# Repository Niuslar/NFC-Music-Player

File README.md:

# NFC Album Player

> **Disclaimer:** the software in this repository was written with an AI coding assistant (Claude Code). The project's idea, hardware choices and design decisions are mine, but I did not hand-write the code, so review it before relying on it.

A tabletop music player where each album is a card. Put a card in the slot and its album plays; take it out and it pauses. It runs on a Raspberry Pi Zero 2 W with a proper DAC, a small screen, a knob and four keys, and keeps a whole music collection on its own SD card. Everything you need to build one is here: the software, the wiring, a 3D-printed case and the circuit board behind its keys.

*Render of the case design, made from the same model as its printable parts. The case has not been printed yet.*

## Where to start

The **[project site](https://niuslar.github.io/NFC-Music-Player/)** has the full guides:

| Guide | What is in it |
|---|---|
| [User manual](https://niuslar.github.io/NFC-Music-Player/docs/manual/) | Using the player: [controls](https://niuslar.github.io/NFC-Music-Player/docs/manual/#controls), [linking your first card](https://niuslar.github.io/NFC-Music-Player/docs/manual/#first-card), [settings](https://niuslar.github.io/NFC-Music-Player/docs/manual/#settings), [adding music](https://niuslar.github.io/NFC-Music-Player/docs/manual/#music), the [web remote](https://niuslar.github.io/NFC-Music-Player/docs/manual/#remote) and [lists](https://niuslar.github.io/NFC-Music-Player/docs/manual/#lists) |
| [Electronics guide](https://niuslar.github.io/NFC-Music-Player/docs/) | Building it: [parts](https://niuslar.github.io/NFC-Music-Player/docs/#parts), [preparing the Pi](https://niuslar.github.io/NFC-Music-Player/docs/#flash), [wiring](https://niuslar.github.io/NFC-Music-Player/docs/#wiring), [the front board](https://niuslar.github.io/NFC-Music-Player/docs/#board), [backups and updates](https://niuslar.github.io/NFC-Music-Player/docs/#backup) and [troubleshooting](https://niuslar.github.io/NFC-Music-Player/docs/#trouble) |
| [3D printing guide](https://niuslar.github.io/NFC-Music-Player/NFC-Player-Case/NFC-Player-Printing.html) | Printing the case parts |
| [Assembly guide](https://niuslar.github.io/NFC-Music-Player/NFC-Player-Case/NFC-Player-Assembly.html) | Putting the electronics into the case |

The software is on the [Releases page](https://github.com/Niuslar/NFC-Music-Player/releases). To try the player before buying anything, run the [simulator](#try-it-without-any-hardware).

## What it does

- **Cards are albums.** Blank NFC cards are linked to albums on the player itself, and each card remembers where it stopped. A card can also play a whole artist, or a list of songs from different albums.
- **Hi-Fi sound.** A Raspberry Pi DAC Pro gives 3.5 mm and RCA outputs.
- **Screen and controls.** A 2-inch screen shows the cover, track and time. The knob sets the volume and scrolls lists; four keys do previous, play/pause, next and back.
- **Standby and power.** A press of the power key puts the player on standby, and a card or any key wakes it at once. Holding it for 2 seconds turns the player off safely.
- **Music over USB.** Plug the player into a computer and its music appears as a drive called `MUSIC`.
- **Web remote.** From any phone or computer on the same Wi-Fi: browse the library, play from any track, link cards, upload or delete music and make lists.
- **Settings on the device.** Join a new Wi-Fi network from a phone, set a volume limit, delete music, or restart.
- **Signed updates over Wi-Fi.** **Firmware update** in the settings installs the newest release. The player checks its signature first, and goes back to the previous version if the new one does not start.

## Status

The electronics and software are done and tested on a real Pi. The case is designed but not yet printed.

- Tested on the Pi: the DAC, NFC reader, knob, keys, power key and light, USB drive mode, setup and the web remote, with the 0.91-inch OLED as the screen. The 2-inch ST7789 screen and joining a new Wi-Fi network from the settings have so far been tried only in the simulator.
- The case's printable parts, drawings and source files are in [NFC-Player-Case](NFC-Player-Case).

## Hardware

| Part | Used here |
|---|---|
| Computer | Raspberry Pi Zero 2 W |
| DAC | Raspberry Pi DAC Pro |
| Display | 2-inch ST7789 SPI LCD, 320×240 (a 0.91-inch SSD1306 I2C OLED also works) |
| NFC reader | PN532 over SPI, with NTAG215 cards |
| Knob | 24-click rotary encoder with push switch |
| Keys | Five momentary push buttons: four for playback, one for power |
| Power light | An LED on GPIO 22 |

The full parts list and wiring are in the [electronics guide](https://niuslar.github.io/NFC-Music-Player/docs/).

## Installing the software

### 1. Download a release

From the [Releases page](https://github.com/Niuslar/NFC-Music-Player/releases), download the three files of the newest release into one folder:

- `nfc-player-X.Y.Z.tar.gz`: the player itself
- `manifest.json`: its version, size and SHA-256 checksum
- `manifest.json.sig`: the signature of the manifest

Only the manifest is signed. Its checksum covers the tarball, so a good signature and a matching checksum together mean the tarball is the one that was released.

### 2. Check it

Do this at least before the first install. A player trusts the release key that comes with the first release you install on it, and from then on installs only updates signed by that key, so checking that first release by hand is what makes every later update safe. Updates from the settings, or with `deploy.sh`, are checked for you.

You need `ssh-keygen` from OpenSSH 8.1 or newer. It comes with macOS, Linux and Windows 10 and 11. If it says `unknown option -- Y`, update OpenSSH.

**The release key.** Save this line as a file called `allowed_signers` in the folder with the three files. It is the same as [`system/allowed_signers`](system/allowed_signers) in this repository.

```text
nfc-player-release namespaces="nfc-player-release" ecdsa-sha2-nistp256 AAAAE2VjZHNhLXNoYTItbmlzdHAyNTYAAAAIbmlzdHAyNTYAAABBBNG2z/+2mxTZ/x4zmyfVjZgFa+9KMFRH0Z7DfmxEzkWDxFyXM+AXKKXkTZ2dmMEVd2C32r4rEvr9HIM9+Vl88ME= nfc-player release
```

Its fingerprint is `SHA256:7mMUd2P1uHX7o64klaQmtPYpVBFrPNvpwkcIh9UWavA`.

**Check the signature.** From that folder, on macOS or Linux, or in the Windows Command Prompt:

```sh
ssh-keygen -Y verify -f allowed_signers -I nfc-player-release -n nfc-player-release -s manifest.json.sig < manifest.json
```

In Windows PowerShell, which has no `<`, run it through the Command Prompt:

```powershell
cmd /c "ssh-keygen -Y verify -f allowed_signers -I nfc-player-release -n nfc-player-release -s manifest.json.sig < manifest.json"
```

A good release prints `Good "nfc-player-release" signature for nfc-player-release with ECDSA key SHA256:7mMUd2P1uHX7o64klaQmtPYpVBFrPNvpwkcIh9UWavA`. Anything else means: do not install it, and download it again.

**Check the checksum.** Print the tarball's SHA-256 and compare it with `"sha256"` in `manifest.json`:

| System | Command |
|---|---|
| macOS | `shasum -a 256 nfc-player-X.Y.Z.tar.gz` |
| Linux | `sha256sum nfc-player-X.Y.Z.tar.gz` |
| Windows | `certutil -hashfile nfc-player-X.Y.Z.tar.gz SHA256` |

They must be the same.

### 3. Install it on a new Pi

1. Prepare the Pi as in the electronics guide: [flash the SD card](https://niuslar.github.io/NFC-Music-Player/docs/#flash) with Raspberry Pi OS Lite (64-bit), hostname `nfcplayer` and SSH turned on, [boot it](https://niuslar.github.io/NFC-Music-Player/docs/#boot) and [fit the DAC](https://niuslar.github.io/NFC-Music-Player/docs/#dac).
2. From the folder with the release, copy it to the Pi and run setup. Replace `X.Y.Z` with the version, and use `yourname@nfcplayer.local` if your user name on the Pi is not the same as on your computer. The commands are the same on Windows, macOS and Linux.

   ```sh
   scp nfc-player-X.Y.Z.tar.gz nfcplayer.local:/tmp/
   ```

   ```sh
   ssh -t nfcplayer.local 'mkdir ~/nfc-player-X.Y.Z && tar -xzf /tmp/nfc-player-X.Y.Z.tar.gz -C ~/nfc-player-X.Y.Z && cd ~/nfc-player-X.Y.Z && sudo system/setup.sh'
   ```

   Setup installs the packages it needs, turns on SPI, I2C and USB drive mode, creates the music drive, and installs the player into `/opt/nfc-player`. It also installs the release key, which is why the release must be checked first.
3. Reboot when setup asks to:

   ```sh
   ssh nfcplayer.local 'sudo reboot'
   ```

4. Carry on with [wiring and testing](https://niuslar.github.io/NFC-Music-Player/docs/#wiring) in the electronics guide. The web remote's **Setup** page, at `http://nfcplayer.local/setup`, chooses the screen and knob and tests each part.

The `~/nfc-player-X.Y.Z` folder on the Pi is not needed after setup and can be deleted.

### Updating

**Firmware update** in the player's settings installs the newest release over Wi-Fi. That is the usual way.

To install a release from your computer instead, for a player with no internet connection or to choose the version yourself, download the three files and copy them over:

```sh
scp nfc-player-X.Y.Z.tar.gz manifest.json manifest.json.sig nfcplayer.local:/tmp/
```

```sh
ssh -t nfcplayer.local 'sudo install -d -o nfc-player /var/lib/nfc-player/update && sudo install -o nfc-player -m 644 /tmp/nfc-player-*.tar.gz /tmp/manifest.json /tmp/manifest.json.sig /var/lib/nfc-player/update/ && sudo /usr/local/sbin/nfc-player-update install'
```

This goes through the same steps as **Firmware update**: the player checks the signature, keeps the version it is running, and goes back to it if the new one does not start. It installs only a version newer than the one running. Card links, lists, settings and music are kept.

### With `deploy.sh`

If you have a copy of this repository on macOS or Linux, `deploy.sh` does the checks and the install in one step, on a new Pi or one that is already set up. It checks the signature and checksum against `system/allowed_signers` before sending anything:

```sh
./deploy.sh --release path/to/folder-with-the-three-files
```

```sh
./deploy.sh --release path/to/folder-with-the-three-files yourname@nfcplayer.local
```

Without `--release`, `deploy.sh` copies the working copy of the code to the Pi, for development.

## Try it without any hardware

The simulator shows the screen in a browser and stands in for the knob, keys, cards, USB port and Wi-Fi. You need Python 3.11 or newer.

```sh
python3 -m venv .venv
.venv/bin/pip install pillow numpy python-mpd2 pytest qrcode
.venv/bin/python -m player.demo_library demo/music
.venv/bin/python -m player.main --sim
```

On Windows, use `py` in place of `python3` and `.venv\Scripts\` in place of `.venv/bin/`.

Open `http://localhost:8137` for the simulated player and `http://localhost:8080` for the web remote. The demo library is generated tones, and the simulator is silent unless you run it with MPD (`system/mpd-dev.sh`, then add `--playback mpd`). Add `--display ssd1306` for the small OLED layout, and `--music path/to/your/music` for your own albums (install `mutagen` too, to read their tags).

Run the tests with:

```sh
.venv/bin/python -m pytest
```

## How it is put together

- `player/app.py` is the player's behaviour: a state machine fed with events from cards, controls, USB and the web.
- `player/ui/render.py` draws the screens.
- `player/hw/` holds the drivers (screens, NFC reader, knob and keys, USB drive mode), the simulator, and checks for each part.
- `player/web/` is the web remote, the Setup page, and the page a phone uses to give the player a new Wi-Fi network.
- `player/playback.py` talks to [MPD](https://www.musicpd.org/), which decodes and plays the music.
- `player/wifi.py` reads the Wi-Fi signal and runs the setup network for joining a new one.
- `player/update.py` and `system/nfc-player-update` do updates. The player keeps two copies of itself, in `/opt/nfc-player/a` and `b`. An update goes into the one that is not running, and the player goes back to the other if the new version does not start.
- `system/` has the Pi's setup script, services, root helpers and the release key.
- `NFC-Player-Case/` is the 3D-printed case and the front board, all generated from the dimensions in `case.py`. Its [README](NFC-Player-Case/README.md) explains how to rebuild them.
- `docs/` and the root `index.html` are the project site, served by GitHub Pages from the root of this repository (so the empty `.nojekyll` file has to stay).

## Contributing

Fixes and ideas are welcome. [CONTRIBUTING.md](CONTRIBUTING.md) covers the simulator, the tests and changing the case. For a bug or an idea, open an [issue](https://github.com/Niuslar/NFC-Music-Player/issues).

## Security

- **Updates** are installed only if they are signed by a key in `/etc/nfc-player/allowed_signers` on the player, which setup copies from the first release installed. See [Check it](#2-check-it).
- **The web remote has no password.** Anyone on the same network as the player can control it and add or delete music, and that includes an open network such as a café's. Use it on a home network you trust, or turn it off with `--web-port 0` in `system/nfc-player.service`.
- **Joining a new Wi-Fi network** is guarded separately: the page that takes the password works only on the player's own setup network, whose password is made up fresh each time and shown only on the player's screen.
- **The player runs as its own system user**, which can run only the player's own helpers with `sudo`, so a bug in it cannot take over the Pi.

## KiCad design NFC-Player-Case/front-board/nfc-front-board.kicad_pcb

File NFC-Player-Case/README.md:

# NFC Player Case

The 3D-printed case for the NFC Album Player, and the small board behind its keys: a perfboard you wire yourself, or a printed circuit board. To print and build it, read the [3D printing guide](https://niuslar.github.io/NFC-Music-Player/NFC-Player-Case/NFC-Player-Printing.html) and the [assembly guide](https://niuslar.github.io/NFC-Music-Player/NFC-Player-Case/NFC-Player-Assembly.html). This page is for changing the design.

Every dimension is in [`case.py`](case.py). The other scripts read it, and everything else in this folder is generated from them, so a change always starts in `case.py`. Do not edit the outputs by hand: the next rebuild overwrites them.

## What is here

**Source**

| File | What it does |
|---|---|
| [`case.py`](case.py) | Every dimension and shape, in millimetres. The values marked MEASURE depend on the parts you bought. |
| [`build.py`](build.py) | Builds the STLs and the OpenSCAD copy with Blender, and checks that no two parts collide. |
| [`keycaps.py`](keycaps.py) | The key carrier: four key caps on one printed frame. `build.py` builds it too. |
| [`wood.py`](wood.py) | Optional: carves wood grain from your own `wood-grain.png` into the sides of the chassis. |
| [`drawings.py`](drawings.py) | Draws the dimensioned SVGs. Plain Python, no Blender. |
| [`pictures.py`](pictures.py) | Draws the assembly pictures for the guides. |
| [`render.py`](render.py) | Renders the hero picture, using the scene in `NFC-Player-Render.blend`. |
| [`guide.py`](guide.py) | Writes the printing and assembly guides, and the front board's section of the [electronics guide](../docs/index.html). |
| [`NFC-Player-Render.blend`](NFC-Player-Render.blend) | The render scene: camera, lights, materials and stand-ins for the bought parts. |
| [`front-board/board.py`](front-board/board.py) | Draws, routes and checks the front board in KiCad, and writes the files to order it. |
| [`front-board/perfboard.py`](front-board/perfboard.py) | Lays out the same board on a 70 x 50 mm perfboard, checks its wiring against `board.py`'s schematic and the spacer's openings, and draws it. Plain Python. |

**Generated, and kept in the repository**

| File | Made by |
|---|---|
| [`STL/`](STL) | `build.py` and `keycaps.py`. These are the parts to print. |
| [`NFC-Player-Case.scad`](NFC-Player-Case.scad) | `build.py`. A copy for OpenSCAD users, not yet tried in OpenSCAD. |
| `Front-Panel.svg`, `Rear-Panel.svg`, `Board-Stack.svg`, `Controls-Section.svg`, `Key-Closeup.svg` | `drawings.py` |
| [`NFC-Player-Render.png`](NFC-Player-Render.png) | `render.py` |
| [`NFC-Player-Printing.html`](NFC-Player-Printing.html), [`NFC-Player-Assembly.html`](NFC-Player-Assembly.html) | `guide.py`. These pages are part of the project site. |
| `front-board/nfc-front-board.*` and [`front-board/fab/`](front-board/fab) | `board.py`. The KiCad project, the checks, and the Gerbers, BOM and placement files to order the board. |
| `front-board/fab/perfboard-back.svg`, `perfboard-front.svg` | `perfboard.py` |

**Generated, only on your computer** (listed in `.gitignore`): `parts.blend`, `pictures/` and the `*-wood.stl` files.

## What you need

Three free programs, on Windows, macOS or Linux:

- [Blender](https://www.blender.org/download/). The scripts were made with Blender 5.2. The commands below call it `blender`: put it on your PATH, or type the full path to the program instead.
- [KiCad](https://www.kicad.org/download/) 10 or later, only for the front board.
- Python 3 with Pillow (`pip install pillow`). Your Python may be called `python`, `python3` or `py`.

`board.py` needs the Python that comes with KiCad, because it uses KiCad's `pcbnew` module. On Windows, run it from the KiCad Command Prompt. On Linux, use the system `python3` that KiCad installs into. On macOS, use the `python3` bundled with KiCad.

## Rebuilding after a change

Edit `case.py`, then run these from this folder, in this order:

```sh
blender -b -P build.py
```

This rewrites the STLs and the OpenSCAD copy, and reports any part that collides with another.

```sh
cd front-board
python board.py
cd ..
```

Do this with KiCad's Python, whenever you move the keys, the screws or the headers. It redraws and reroutes the board, runs KiCad's electrical and design rules checks, and rewrites the files in `fab/`.

```sh
cd front-board
python perfboard.py
cd ..
```

This redraws the perfboard version and checks its wiring. Any Python 3 will do.

```sh
blender -b -P wood.py
```

This one is only needed for the wood-grain chassis.

```sh
python drawings.py
```

```sh
blender -b -P pictures.py
```

```sh
blender -b NFC-Player-Render.blend -P render.py
```

```sh
python guide.py
```

The checks in `build.py` prove that the parts fit each other and the stand-ins for the boards. They cannot check print tolerances, your exact boards, heat, or how well the NFC reader works next to stored cards. Those need a bench test.

The STLs, render and guides are large. Commit regenerated copies when a change is finished, not after every trial run: each copy stays in the repository's history for good.

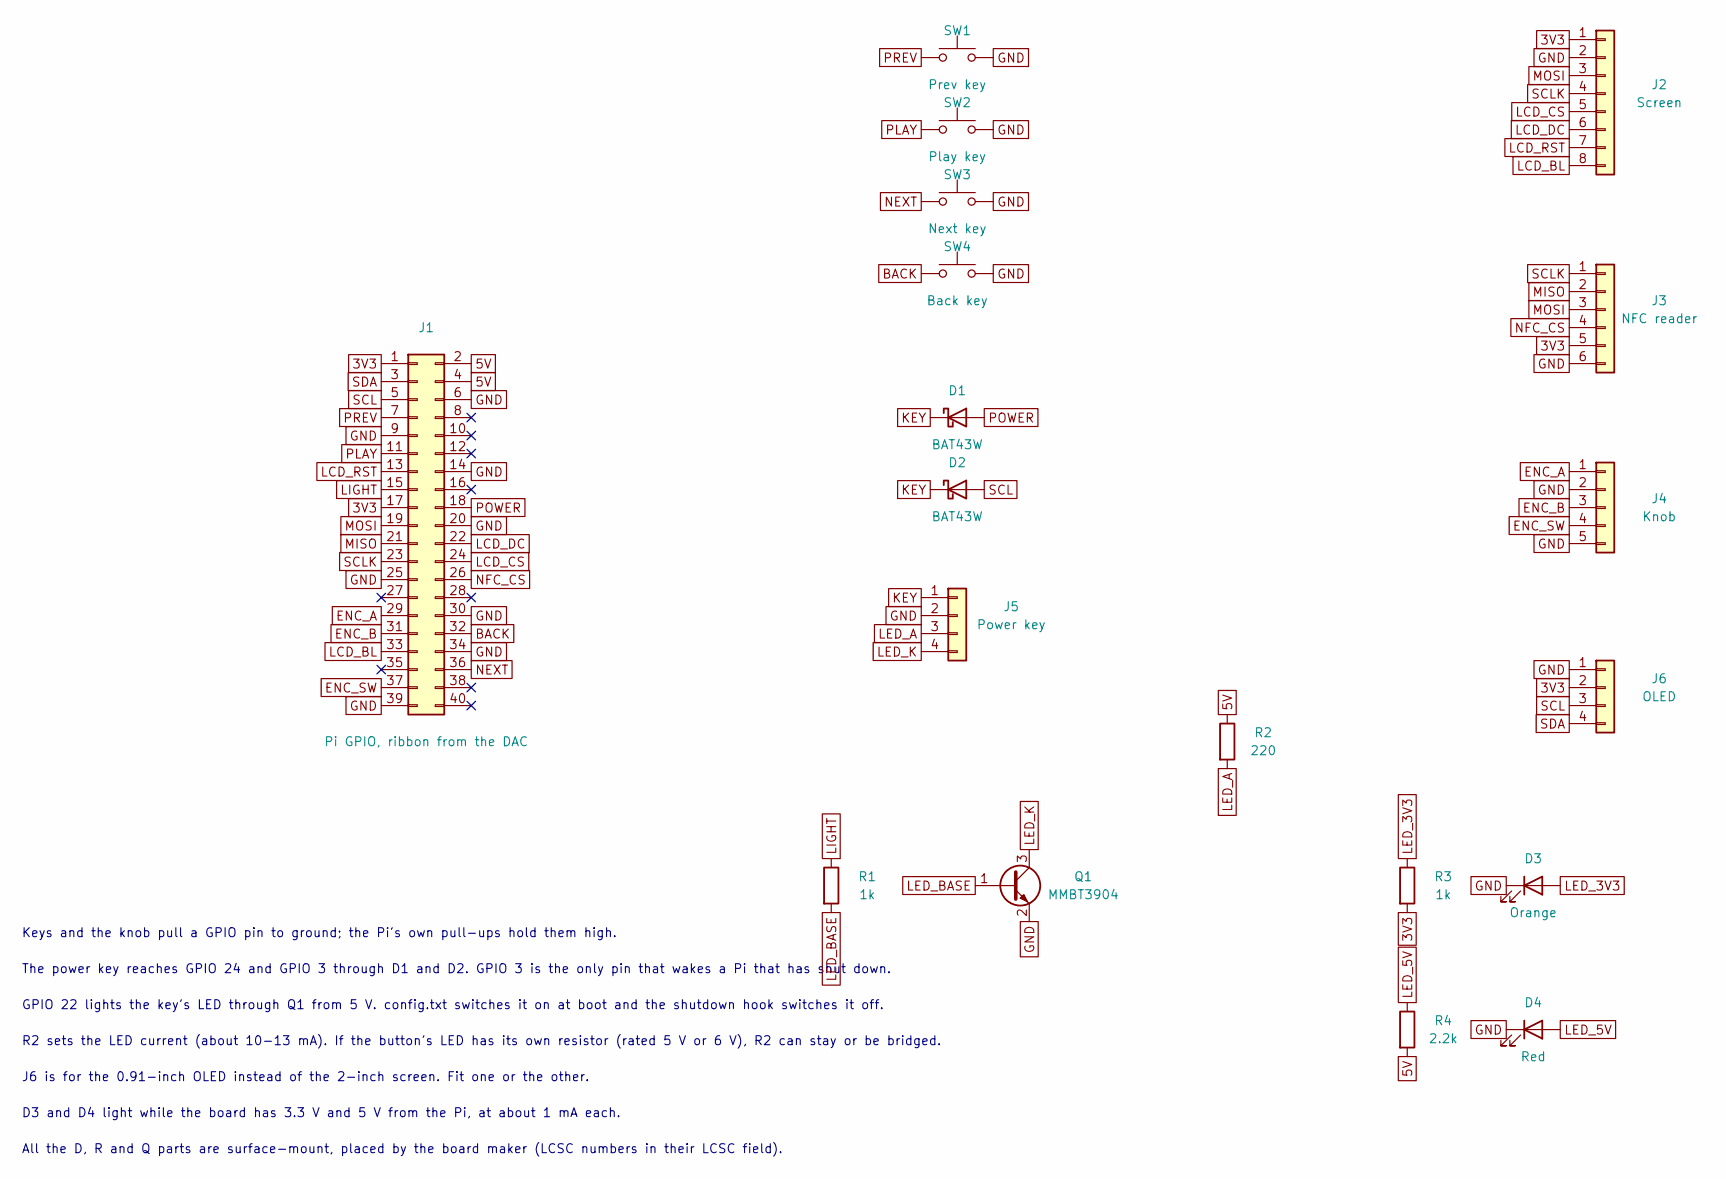
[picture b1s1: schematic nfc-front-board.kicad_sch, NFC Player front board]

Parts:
D1, D2: BAT43W; D_SOD-123; LCSC C19167
D3: Orange; LED_0603_1608Metric; LCSC C160478
D4: Red; LED_0603_1608Metric; LCSC C2286
J1: Pi GPIO, ribbon from the DAC; IDC-Header_2x20_P2.54mm_Vertical
J2: Screen; PinHeader_1x08_P2.54mm_Vertical
J3: NFC reader; PinHeader_1x06_P2.54mm_Vertical
J4: Knob; PinHeader_1x05_P2.54mm_Vertical
J5: Power key; PinHeader_1x04_P2.54mm_Vertical
J6: OLED; PinHeader_1x04_P2.54mm_Vertical
Q1: MMBT3904; SOT-23; LCSC C20526
R1, R3: 1k; R_0603_1608Metric; LCSC C21190
R2: 220; R_0603_1608Metric; LCSC C22962
R4: 2.2k; R_0603_1608Metric; LCSC C4190
SW1: Prev key; SW_PUSH_6mm_H5mm
SW2: Play key; SW_PUSH_6mm_H5mm
SW3: Next key; SW_PUSH_6mm_H5mm
SW4: Back key; SW_PUSH_6mm_H5mm

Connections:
3V3: J1.1, J1.17, J2.1, J3.5, J6.2, R3.2
5V: J1.2, J1.4, R2.1, R4.2
BACK: J1.32, SW4.1
ENC_A: J1.29, J4.1
ENC_B: J1.31, J4.3
ENC_SW: J1.37, J4.4
GND: D3.1 (K), D4.1 (K), J1.6, J1.9, J1.14, J1.20, J1.25, J1.30, J1.34, J1.39, J2.2, J3.6, J4.2, J4.5, J5.2, J6.1, Q1.2 (E), SW1.2, SW2.2, SW3.2, SW4.2
KEY: D1.1 (K), D2.1 (K), J5.1
LCD_BL: J1.33, J2.8
LCD_CS: J1.24, J2.5
LCD_DC: J1.22, J2.6
LCD_RST: J1.13, J2.7
LED_3V3: D3.2 (A), R3.1
LED_5V: D4.2 (A), R4.1
LED_A: J5.3, R2.2
LED_BASE: Q1.1 (B), R1.2
LED_K: J5.4, Q1.3 (C)
LIGHT: J1.15, R1.1
MISO: J1.21, J3.2
MOSI: J1.19, J2.3, J3.3
NEXT: J1.36, SW3.1
NFC_CS: J1.26, J3.4
PLAY: J1.11, SW2.1
POWER: D1.2 (A), J1.18
PREV: J1.7, SW1.1
SCL: D2.2 (A), J1.5, J6.3
SCLK: J1.23, J2.4, J3.1
SDA: J1.3, J6.4

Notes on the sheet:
Keys and the knob pull a GPIO pin to ground; the Pi's own pull-ups hold them high.
The power key reaches GPIO 24 and GPIO 3 through D1 and D2. GPIO 3 is the only pin that wakes a Pi that has shut down.
GPIO 22 lights the key's LED through Q1 from 5 V. config.txt switches it on at boot and the shutdown hook switches it off.
R2 sets the LED current (about 10-13 mA). If the button's LED has its own resistor (rated 5 V or 6 V), R2 can stay or be bridged.
J6 is for the 0.91-inch OLED instead of the 2-inch screen. Fit one or the other.
D3 and D4 light while the board has 3.3 V and 5 V from the Pi, at about 1 mA each.
All the D, R and Q parts are surface-mount, placed by the board maker (LCSC numbers in their LCSC field).

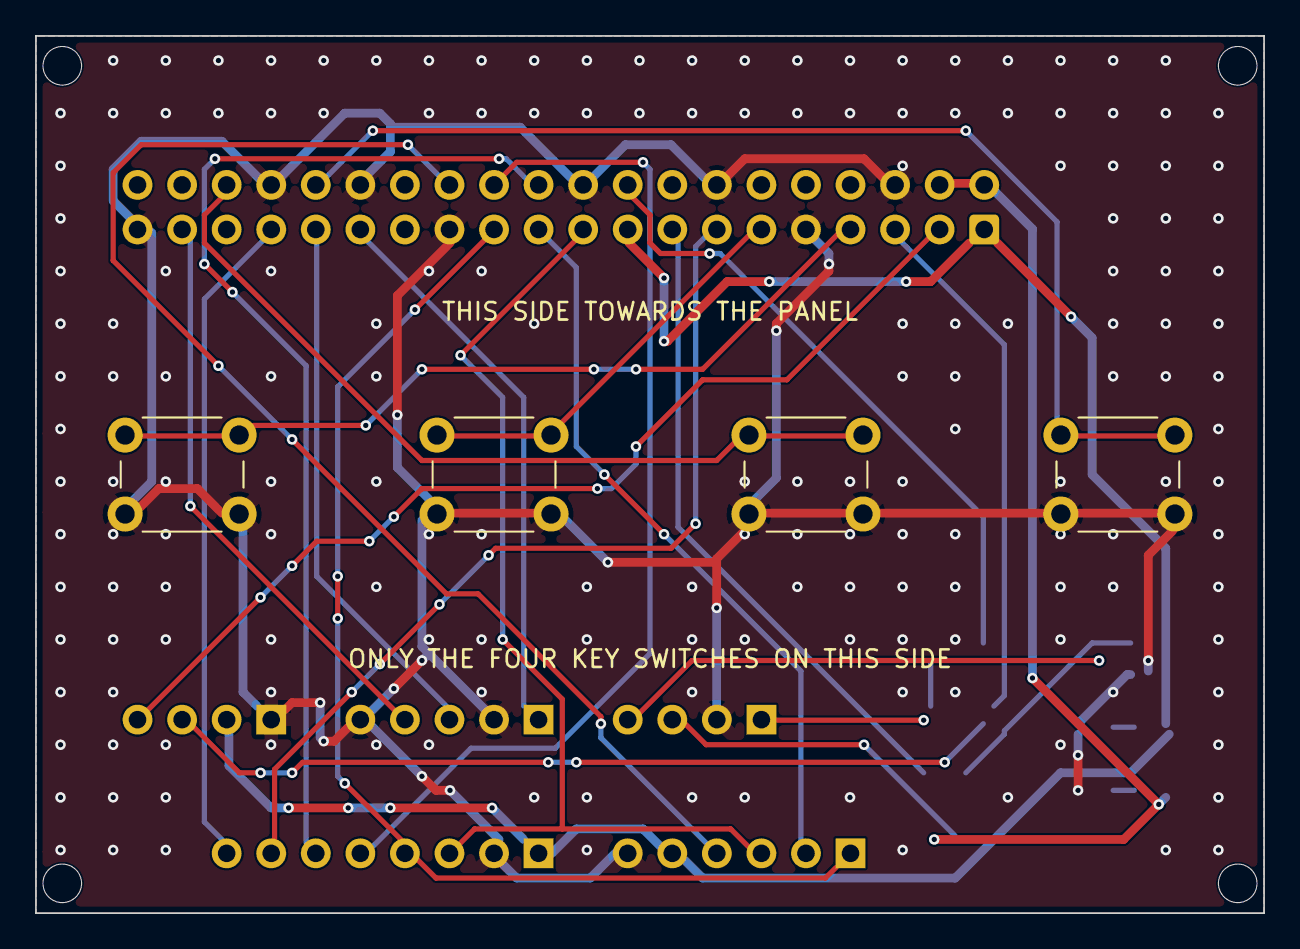
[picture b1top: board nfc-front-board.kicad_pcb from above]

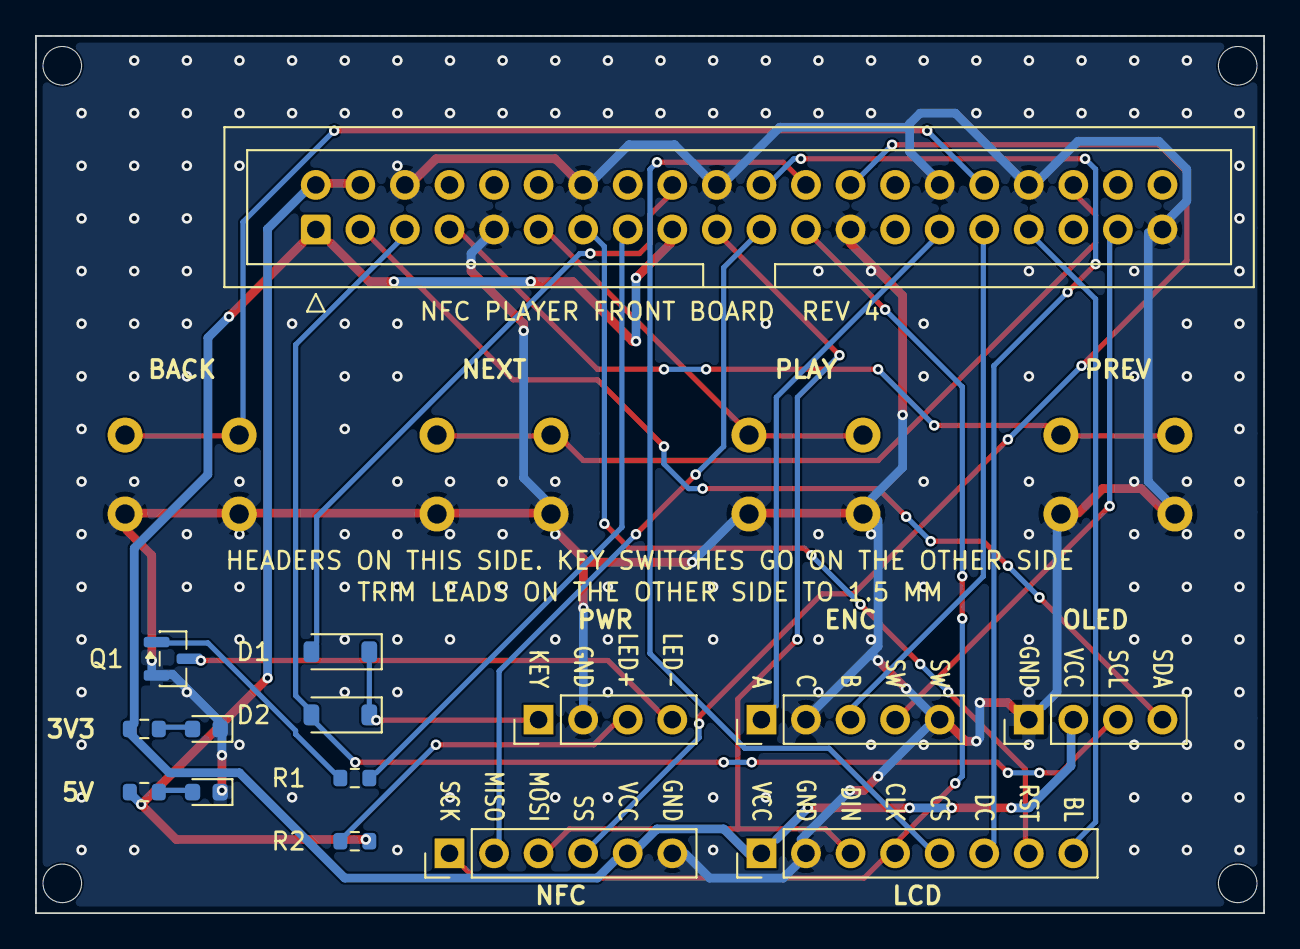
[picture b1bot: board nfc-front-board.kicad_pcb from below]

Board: 2 copper layers, 70.0 x 50.0 mm, 23 parts (15 on the bottom side), 28 nets.

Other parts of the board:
H1, H2, H3, H4: MountingHole_2.2mm_M2

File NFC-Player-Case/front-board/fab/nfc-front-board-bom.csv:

"Refs","Value","Footprint","Description","Qty"
"D1,D2","BAT43W","Diode_SMD:D_SOD-123","Small-signal Schottky diode, 30 V 200 mA, SOD-123. Cathode towards the key","2"
"D3","Orange","LED_SMD:LED_0603_1608Metric","Orange LED, 0603 (Lite-On LTST-C191KFKT): lit while the board has 3.3 V","1"
"D4","Red","LED_SMD:LED_0603_1608Metric","Red LED, 0603: lit while the board has 5 V","1"
"J1","Pi GPIO, ribbon from the DAC","Connector_IDC:IDC-Header_2x20_P2.54mm_Vertical","Shrouded 2x20 box header, 2.54 mm","1"
"J2","Screen","Connector_PinHeader_2.54mm:PinHeader_1x08_P2.54mm_Vertical","Straight pin header, 2.54 mm","1"
"J3","NFC reader","Connector_PinHeader_2.54mm:PinHeader_1x06_P2.54mm_Vertical","Straight pin header, 2.54 mm","1"
"J4","Knob","Connector_PinHeader_2.54mm:PinHeader_1x05_P2.54mm_Vertical","Straight pin header, 2.54 mm","1"
"J5","Power key","Connector_PinHeader_2.54mm:PinHeader_1x04_P2.54mm_Vertical","Straight pin header, 2.54 mm","1"
"J6","OLED","Connector_PinHeader_2.54mm:PinHeader_1x04_P2.54mm_Vertical","Straight pin header, 2.54 mm","1"
"Q1","MMBT3904","Package_TO_SOT_SMD:SOT-23","NPN transistor, SOT-23. Switches the power light from 5 V","1"
"R1,R3","1k","Resistor_SMD:R_0603_1608Metric","1 kΩ 1% 0603: about 1 mA through D3,Base resistor, 1 kΩ 1% 0603","2"
"R2","220","Resistor_SMD:R_0603_1608Metric","Sets the power light's current, 220 Ω 1% 0603. If the button's LED has its own resistor, R2 can stay (a little dimmer) or be bridged with solder","1"
"R4","2.2k","Resistor_SMD:R_0603_1608Metric","2.2 kΩ 1% 0603: about 1 mA through D4","1"
"SW1","Prev key","Button_Switch_THT:SW_PUSH_6mm_H5mm","6 x 6 mm through-hole tactile switch, 5 mm tall, on the side facing the panel","1"
"SW2","Play key","Button_Switch_THT:SW_PUSH_6mm_H5mm","6 x 6 mm through-hole tactile switch, 5 mm tall, on the side facing the panel","1"
"SW3","Next key","Button_Switch_THT:SW_PUSH_6mm_H5mm","6 x 6 mm through-hole tactile switch, 5 mm tall, on the side facing the panel","1"
"SW4","Back key","Button_Switch_THT:SW_PUSH_6mm_H5mm","6 x 6 mm through-hole tactile switch, 5 mm tall, on the side facing the panel","1"

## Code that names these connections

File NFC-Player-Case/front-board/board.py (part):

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
The board lies flat on a printed spacer behind the front panel, behind the four keys. The keys'
6 x 6 mm tactile switches are soldered on its front, facing the panel, where the key caps press
them. The pin headers are through-hole on the back and soldered on the front; the spacer has
openings under those joints. The small parts (diodes, resistors, transistor and the two LEDs that
show 3.3 V and 5 V) are surface-mount on the back, placed by the board maker: fab/ gets a BOM and
a placement file in JLCPCB's format, with LCSC part numbers, beside the Gerbers.
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}
POWER_NETS = ("GND", "3V3", "5V")

# Headers on the back of the board, pin 1 first, in the holes case.HEADER_HOLES gives. Pin names are printed beside the pins.
HEADERS = {
    # ref: (title, pin names, nets, pin 1 x, z, value)
    "J2": ("LCD", ("VCC", "GND", "DIN", "CLK", "CS", "DC", "RST", "BL"), ("3V3", "GND", "MOSI", "SCLK", "LCD_CS", "LCD_DC", "LCD_RST", "LCD_BL"), *c.hole(*c.HEADER_HOLES["J2"]), "Screen"),
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    return str(uuid.uuid5(uuid.NAMESPACE_URL, f"nfc-front-board/{next(_UIDS)}"))


def part(ref, value, symbol, footprint, nets, at, side="back", rot=0.0, desc="", lcsc=None, label=None, box=None):
    """lcsc: the LCSC part number for a part the board maker places. label: (x, y) of its name on the
    back's silkscreen. box: (length, width, height) of its body, from its pad 1, for the case pictures."""
    PARTS.append({"ref": ref, "value": value, "symbol": symbol, "footprint": footprint, "nets": nets, "at": at, "side": side, "rot": rot, "desc": desc,
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     desc="Small-signal Schottky diode, 30 V 200 mA, SOD-123. Cathode towards the key")
part("D2", "BAT43W", ("Device", "D_Schottky"), SOD123, {"1": "KEY", "2": "SCL"}, (80.0, 44.2), lcsc="C19167", label=(86.6, 44.2), box=(3.7, 1.6, 1.1),
     desc="Small-signal Schottky diode, 30 V 200 mA, SOD-123. Cathode towards the key")
part("R1", "1k", ("Device", "R"), R0603, {"1": "LIGHT", "2": "LED_BASE"}, (80.0, 47.8), lcsc="C21190", label=(84.6, 47.8), box=(1.6, 0.8, 0.5),
     desc="Base resistor, 1 kΩ 1% 0603")
part("R2", "220", ("Device", "R"), R0603, {"1": "5V", "2": "LED_A"}, (80.0, 51.4), lcsc="C22962", label=(84.6, 51.4), box=(1.6, 0.8, 0.5),
     desc="Sets the power light's current, 220 Ω 1% 0603. If the button's LED has its own resistor, R2 can stay (a little dimmer) or be bridged with solder")
part("Q1", "MMBT3904", ("Transistor_BJT", "Q_NPN_BEC"), ("Package_TO_SOT_SMD", "SOT-23"), {"1": "LED_BASE", "2": "GND", "3": "LED_K"}, (91.5, 41.0),
     lcsc="C20526", label=(95.0, 41.0), box=(2.9, 1.3, 1.0), desc="NPN transistor, SOT-23. Switches the power light from 5 V")
part("D3", "Orange", ("Device", "LED"), LED0603, {"1": "GND", "2": "LED_3V3"}, (88.5, 45.0), lcsc="C160478", label=(97.0, 45.0), box=(1.6, 0.8, 0.6),
     desc="Orange LED, 0603 (Lite-On LTST-C191KFKT): lit while the board has 3.3 V")
part("R3", "1k", ("Device", "R"), R0603, {"1": "LED_3V3", "2": "3V3"}, (92.0, 45.0), lcsc="C21190", box=(1.6, 0.8, 0.5),
     desc="1 kΩ 1% 0603: about 1 mA through D3")
part("D4", "Red", ("Device", "LED"), LED0603, {"1": "GND", "2": "LED_5V"}, (88.5, 48.6), lcsc="C2286", label=(96.6, 48.6), box=(1.6, 0.8, 0.6),
     desc="Red LED, 0603: lit while the board has 5 V")
part("R4", "2.2k", ("Device", "R"), R0603, {"1": "LED_5V", "2": "5V"}, (92.0, 48.6), lcsc="C4190", box=(1.6, 0.8, 0.5),
     desc="2.2 kΩ 1% 0603: about 1 mA through D4")
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        board.Add(t)
        return t

    # labels on the back, for the person plugging things in: header names, pin names, keys
    for ref, (title, names, netl, x1p, z, value) in HEADERS.items():
        y = Y(z)
        for k, name in enumerate(names):
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
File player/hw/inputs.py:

"""Knob and buttons on the Pi's GPIO pins.

The encoder is decoded on every edge with lgpio (fast, level comes with the
edge), and movement is sent on as one Rotate event every 20 ms.
"""

import threading
import time

from .. import events as ev
from ..knob import COUNTS_PER_REV

# Quadrature transitions: index is (previous AB << 2) | current AB.
_STEP = (0, -1, 1, 0, 1, 0, 0, -1, -1, 0, 0, 1, 0, 1, -1, 0)

ENCODERS = {
    # name: (pulses per revolution, use the Pi's pull-ups, debounce in microseconds)
    "pec11": (24, True, 800),  # clicky mechanical encoder, 24 clicks per turn, contacts to ground
    "em14": (64, False, 0),  # smooth optical encoder, driven outputs through 5 V -> 3.3 V dividers
}
# Volume steps per turn: two per click on the clicky one, so every click feels the same.
VOLUME_STEPS_PER_REV = {"pec11": 48, "em14": 60}


class Quadrature:
    """Pure decoder: feed pin levels, collect counts scaled to COUNTS_PER_REV."""

    def __init__(self, ppr: int, reverse: bool = False):
        self._scale = COUNTS_PER_REV / (4 * ppr) * (-1 if reverse else 1)
        self._state = 0
        self._edges = 0
        self._lock = threading.Lock()

    def update(self, a: int, b: int) -> None:
        state = (a << 1) | b
        with self._lock:
            self._edges += _STEP[(self._state << 2) | state]
            self._state = state

    def take(self) -> float:
        with self._lock:
            edges, self._edges = self._edges, 0
        return edges * self._scale


class Encoder:
    def __init__(self, event_queue, pin_a: int, pin_b: int, kind: str = "pec11", reverse: bool = False):
        import lgpio

        ppr, pull_up, debounce = ENCODERS[kind]
        self.queue = event_queue
        self.decoder = Quadrature(ppr, reverse)
        self._lg, self._pins = lgpio, (pin_a, pin_b)
        self._chip = lgpio.gpiochip_open(0)
        flags = lgpio.SET_PULL_UP if pull_up else lgpio.SET_PULL_NONE
        self._levels = {}
        self._callbacks = []
        for pin in self._pins:
            lgpio.gpio_claim_alert(self._chip, pin, lgpio.BOTH_EDGES, flags)
            if debounce:
                lgpio.gpio_set_debounce_micros(self._chip, pin, debounce)
            self._levels[pin] = lgpio.gpio_read(self._chip, pin)
            self._callbacks.append(lgpio.callback(self._chip, pin, lgpio.BOTH_EDGES, self._edge))
        self.decoder.update(self._levels[pin_a], self._levels[pin_b])
        self.decoder.take()
        threading.Thread(target=self._flush, daemon=True).start()

    def _edge(self, chip, pin, level, tick) -> None:
        if level in (0, 1):  # 2 is a watchdog timeout, not an edge
            self._levels[pin] = level
            self.decoder.update(self._levels[self._pins[0]], self._levels[self._pins[1]])

    def _flush(self) -> None:
        while True:
            time.sleep(0.02)
            counts = self.decoder.take()
            if counts:
                self.queue.put(ev.Rotate(counts))


# Buttons that do something different when held: a short press is sent on release instead.
HOLD_NAMES = {"knob": "knob_long", "back": "back_long", "prev": "prev_hold", "next": "next_hold", "power": "power_long"}
# Restarting the album and turning the Pi right off are drastic: they need a deliberate hold.
HOLD_SECONDS = {"back": 2.0, "power": 2.0, "knob": 1.0}
REPEATS = {"prev", "next"}  # these keep sending their hold event while held, to scan through a track


class Buttons:
    """buttons maps a name (prev, play, next, back, power) to its GPIO; knob is the encoder's push switch.

    The knob sends knob_long once after 1 second; back and power send back_long / power_long once after 2 seconds. Previous and next
    send prev_hold / next_hold every scan_seconds while held, and nothing on release; a short press sends the plain name.
    """

    def __init__(self, event_queue, knob_pin: int, buttons: dict[str, int], hold_seconds: float = 0.6, scan_seconds: float = 0.4):
        from gpiozero import Button

        self.queue = event_queue
        self._held: dict[str, bool] = {}
        self._devices = []
        for name, pin in {"knob": knob_pin, **buttons}.items():
            if name in HOLD_NAMES:
                repeat = name in REPEATS
                b = Button(pin, pull_up=True, bounce_time=0.02, hold_time=scan_seconds if repeat else HOLD_SECONDS.get(name, hold_seconds), hold_repeat=repeat)
                b.when_held = lambda name=name: self.held(name)
                b.when_released = lambda name=name: self.released(name)
            else:
                b = Button(pin, pull_up=True, bounce_time=0.02)
                b.when_pressed = lambda name=name: self.queue.put(ev.Press(name))
            self._devices.append(b)

    def held(self, name: str) -> None:
        self._held[name] = True
        self.queue.put(ev.Press(HOLD_NAMES[name]))

    def released(self, name: str) -> None:
        if not self._held.get(name):
            self.queue.put(ev.Press(name))
        self._held[name] = False
